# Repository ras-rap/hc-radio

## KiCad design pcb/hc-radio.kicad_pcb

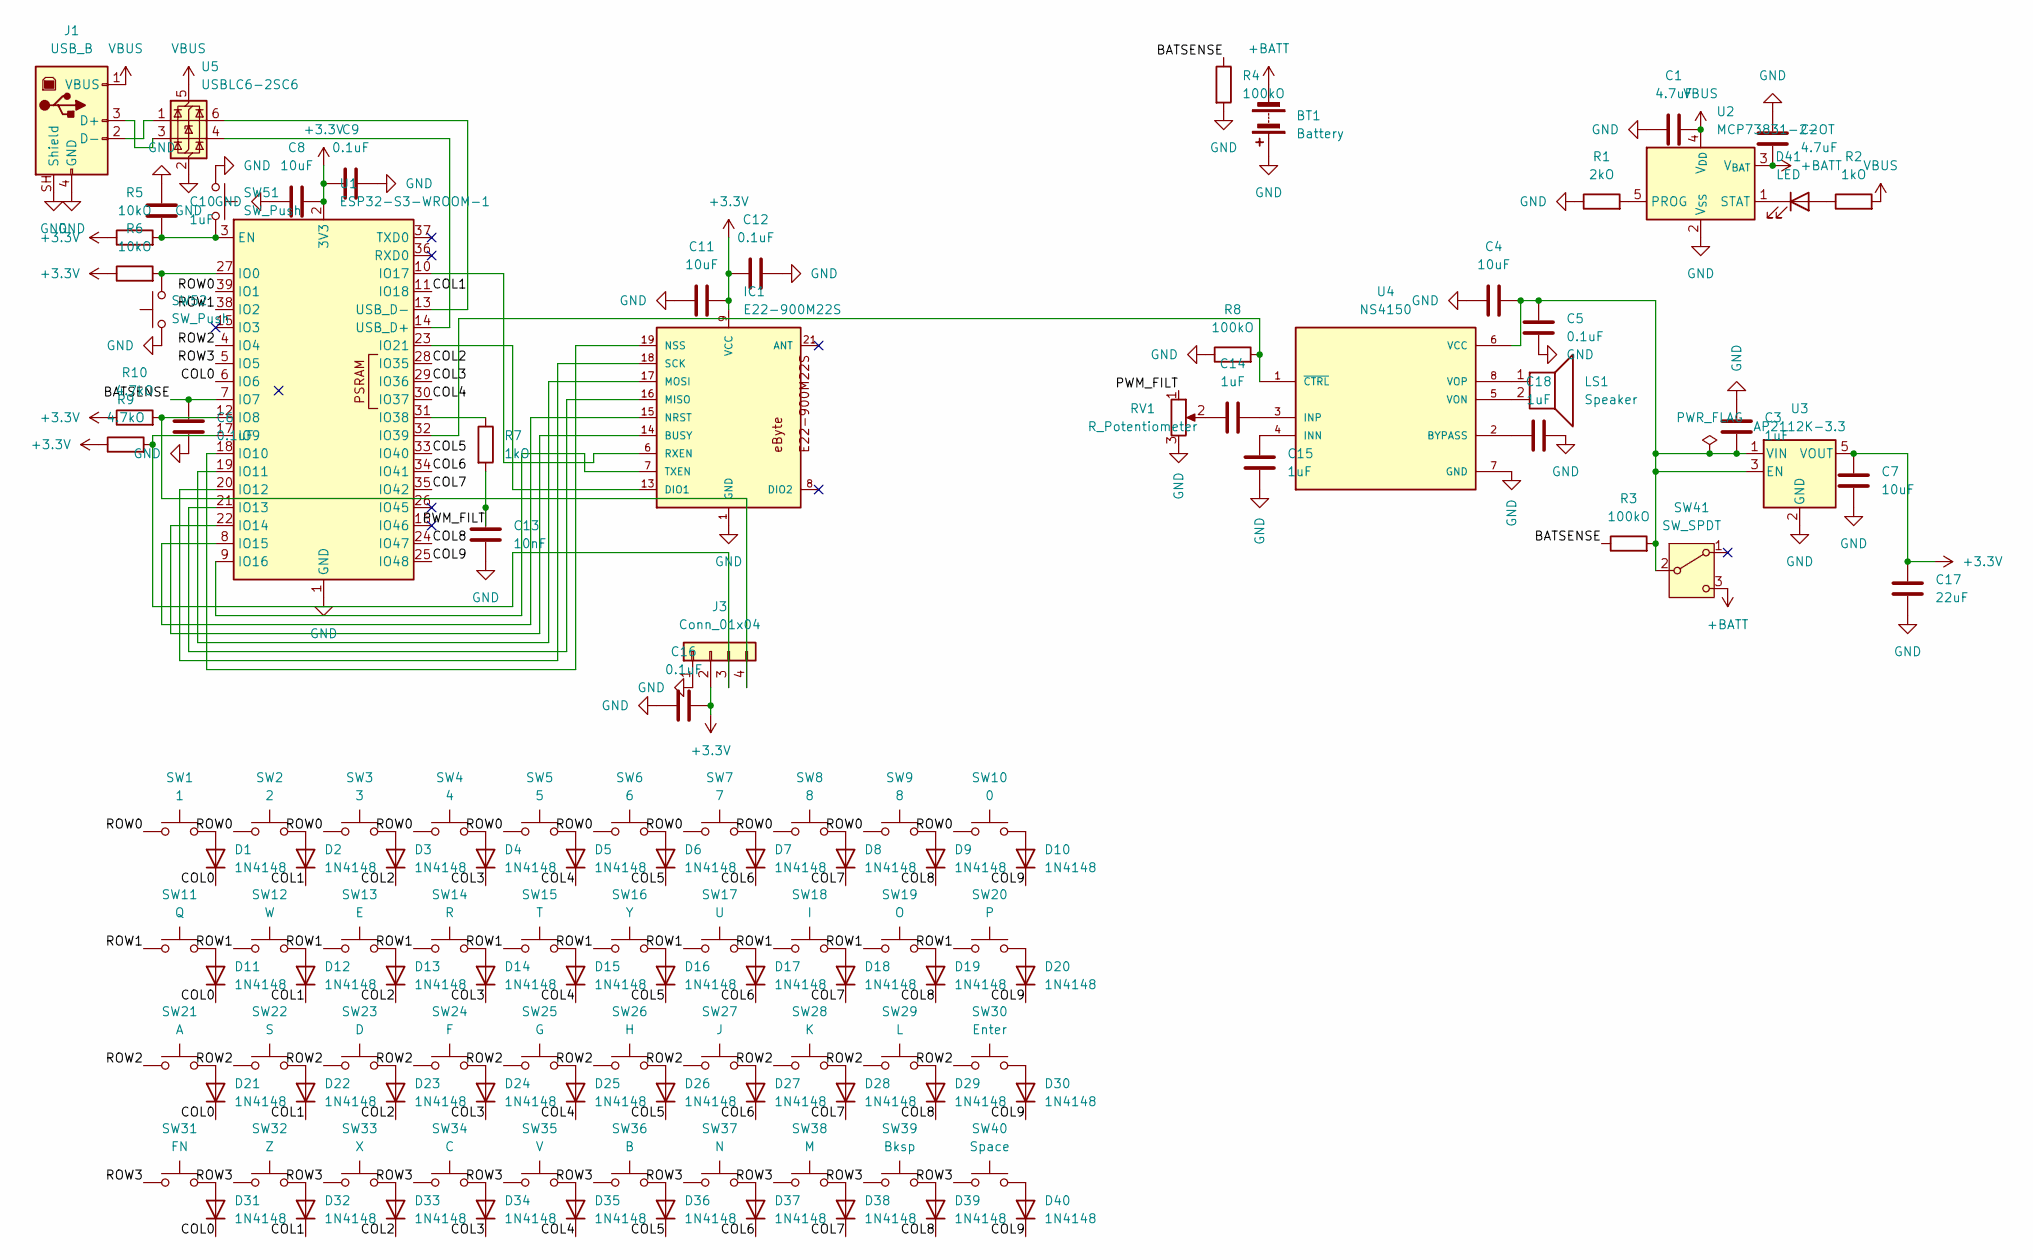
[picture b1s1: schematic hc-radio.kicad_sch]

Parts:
BT1: Battery; JST_PH_B2B-PH-K_1x02_P2.00mm_Vertical
C1, C2: 4.7uF; C_0805_2012Metric_Pad1.18x1.45mm_HandSolder
C3, C10, C14, C15, C18: 1uF; C_0805_2012Metric_Pad1.18x1.45mm_HandSolder
C4, C7, C8, C11: 10uF; C_0805_2012Metric_Pad1.18x1.45mm_HandSolder
C5, C6, C9, C12, C16: 0.1uF; C_0805_2012Metric_Pad1.18x1.45mm_HandSolder
C13: 10nF; C_0805_2012Metric_Pad1.18x1.45mm_HandSolder
C17: 22uF; C_0805_2012Metric_Pad1.18x1.45mm_HandSolder
D1, D2, D3, D4, D5, D6, D7, D8, D9, D10, D11, D12, D13, D14, D15, D16, D17, D18, D19, D20, D21, D22, D23, D24, D25, D26, D27, D28, D29, D30, D31, D32, D33, D34, D35, D36, D37, D38, D39, D40: 1N4148; D_DO-35_SOD27_P7.62mm_Horizontal
D41: LED; LED_D3.0mm
IC1: E22-900M22S
J1: USB_B; USB_B_Lumberg_2411_02_Horizontal
J3: Conn_01x04; PinHeader_1x04_P2.54mm_Vertical
LS1: Speaker; JST_EH_B2B-EH-A_1x02_P2.50mm_Vertical
R1: 2kO; R_0805_2012Metric_Pad1.20x1.40mm_HandSolder
R2, R7: 1kO; R_0805_2012Metric_Pad1.20x1.40mm_HandSolder
R3, R4, R8: 100kO; R_0805_2012Metric_Pad1.20x1.40mm_HandSolder
R5, R6: 10kO; R_0805_2012Metric_Pad1.20x1.40mm_HandSolder
R9, R10: 4.7kO; R_0805_2012Metric_Pad1.20x1.40mm_HandSolder
RV1: R_Potentiometer; Potentiometer_Alps_RK163_Single_Horizontal
SW1: 1; SW_PUSH_6mm
SW2: 2; SW_PUSH_6mm
SW3: 3; SW_PUSH_6mm
SW4: 4; SW_PUSH_6mm
SW5: 5; SW_PUSH_6mm
SW6: 6; SW_PUSH_6mm
SW7: 7; SW_PUSH_6mm
SW8, SW9: 8; SW_PUSH_6mm
SW10: 0; SW_PUSH_6mm
SW11: Q; SW_PUSH_6mm
SW12: W; SW_PUSH_6mm
SW13: E; SW_PUSH_6mm
SW14: R; SW_PUSH_6mm
SW15: T; SW_PUSH_6mm
SW16: Y; SW_PUSH_6mm
SW17: U; SW_PUSH_6mm
SW18: I; SW_PUSH_6mm
SW19: O; SW_PUSH_6mm
SW20: P; SW_PUSH_6mm
SW21: A; SW_PUSH_6mm
SW22: S; SW_PUSH_6mm
SW23: D; SW_PUSH_6mm
SW24: F; SW_PUSH_6mm
SW25: G; SW_PUSH_6mm
SW26: H; SW_PUSH_6mm
SW27: J; SW_PUSH_6mm
SW28: K; SW_PUSH_6mm
SW29: L; SW_PUSH_6mm
SW30: Enter; SW_PUSH_6mm
SW31: FN; SW_PUSH_6mm
SW32: Z; SW_PUSH_6mm
SW33: X; SW_PUSH_6mm
SW34: C; SW_PUSH_6mm
SW35: V; SW_PUSH_6mm
SW36: B; SW_PUSH_6mm
SW37: N; SW_PUSH_6mm
SW38: M; SW_PUSH_6mm
SW39: Bksp; SW_PUSH_6mm
SW40: Space; SW_PUSH_6mm
SW41: SW_SPDT; SW_Slide_SPDT_Straight_CK_OS102011MS2Q
SW51, SW52: SW_Push; SW_PUSH_6mm
U1: ESP32-S3-WROOM-1
U2: MCP73831-2-OT; SOT-23-5
U3: AP2112K-3.3; SOT-23-5
U4: NS4150; SOIC-8_3.9x4.9mm_P1.27mm; PARTREV 1.1
U5: USBLC6-2SC6; SOT-23-6

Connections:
+3.3V: C7.1, C8.2, C9.1, C11.2, C12.1, C16.2, C17.1, IC1.9 (VCC), J3.2, R5.1, R6.1, R9.1, R10.1, U1.2 (3V3), U3.5 (VOUT)
+BATT: BT1.2 (-), C2.2, SW41.3 (C), U2.3 (V_{BAT})
/BATSENSE: C6.1, R3.1, R4.1, U1.7 (IO7)
/COL0: D1.1 (K), D11.1 (K), D21.1 (K), D31.1 (K), U1.6 (IO6)
/COL1: D2.1 (K), D12.1 (K), D22.1 (K), D32.1 (K), U1.11 (IO18)
/COL2: D3.1 (K), D13.1 (K), D23.1 (K), D33.1 (K), U1.28 (IO35)
/COL3: D4.1 (K), D14.1 (K), D24.1 (K), D34.1 (K), U1.29 (IO36)
/COL4: D5.1 (K), D15.1 (K), D25.1 (K), D35.1 (K), U1.30 (IO37)
/COL5: D6.1 (K), D16.1 (K), D26.1 (K), D36.1 (K), U1.33 (IO40)
/COL6: D7.1 (K), D17.1 (K), D27.1 (K), D37.1 (K), U1.34 (IO41)
/COL7: D8.1 (K), D18.1 (K), D28.1 (K), D38.1 (K), U1.35 (IO42)
/COL8: D9.1 (K), D19.1 (K), D29.1 (K), D39.1 (K), U1.24 (IO47)
/COL9: D10.1 (K), D20.1 (K), D30.1 (K), D40.1 (K), U1.25 (IO48)
/PWM_FILT: C13.1, R7.2, RV1.1
/ROW0: SW1.1, SW2.1, SW3.1, SW4.1, SW5.1, SW6.1, SW7.1, SW8.1, SW9.1, SW10.1, U1.39 (IO1)
/ROW1: SW11.1, SW12.1, SW13.1, SW14.1, SW15.1, SW16.1, SW17.1, SW18.1, SW19.1, SW20.1, U1.38 (IO2)
/ROW2: SW21.1, SW22.1, SW23.1, SW24.1, SW25.1, SW26.1, SW27.1, SW28.1, SW29.1, SW30.1, U1.4 (IO4)
/ROW3: SW31.1, SW32.1, SW33.1, SW34.1, SW35.1, SW36.1, SW37.1, SW38.1, SW39.1, SW40.1, U1.5 (IO5)
GND: BT1.1 (+), C1.1, C2.1, C3.1, C4.1, C5.2, C6.2, C7.2, C8.1, C9.2, C10.2, C11.1, C12.2, C13.2, C15.2, C16.1, C17.2, C18.1, IC1.1 (GND), IC1.2 (GND), IC1.3 (GND), IC1.4 (GND), IC1.5 (GND), IC1.10 (GND), IC1.11 (GND), IC1.12 (GND), IC1.20 (GND), IC1.22 (GND), J1.4 (GND), J1.SH (Shield), J3.1, R1.1, R4.2, R8.1, RV1.3, SW51.1, SW52.1, U1.1 (GND), U1.40 (GND), U1.41 (GND), U2.2 (V_{SS}), U3.2 (GND), U4.7 (GND), U5.2 (GND)
unnamed: C14.2, RV1.2
unnamed: D1.2 (A), SW1.2
unnamed: D2.2 (A), SW2.2
unnamed: D3.2 (A), SW3.2
unnamed: D4.2 (A), SW4.2
unnamed: D5.2 (A), SW5.2
unnamed: D6.2 (A), SW6.2
unnamed: D7.2 (A), SW7.2
unnamed: D8.2 (A), SW8.2
unnamed: D9.2 (A), SW9.2
unnamed: D10.2 (A), SW10.2
unnamed: D11.2 (A), SW11.2
unnamed: D12.2 (A), SW12.2
unnamed: D13.2 (A), SW13.2
unnamed: D14.2 (A), SW14.2
unnamed: D15.2 (A), SW15.2
unnamed: D16.2 (A), SW16.2
unnamed: D17.2 (A), SW17.2
unnamed: D18.2 (A), SW18.2
unnamed: D19.2 (A), SW19.2
unnamed: D20.2 (A), SW20.2
unnamed: D21.2 (A), SW21.2
unnamed: D22.2 (A), SW22.2
unnamed: D23.2 (A), SW23.2
unnamed: D24.2 (A), SW24.2
unnamed: D25.2 (A), SW25.2
unnamed: D26.2 (A), SW26.2
unnamed: D27.2 (A), SW27.2
unnamed: D28.2 (A), SW28.2
unnamed: D29.2 (A), SW29.2
unnamed: D30.2 (A), SW30.2
unnamed: D31.2 (A), SW31.2
unnamed: D32.2 (A), SW32.2
unnamed: D33.2 (A), SW33.2
unnamed: D34.2 (A), SW34.2
unnamed: D35.2 (A), SW35.2
unnamed: D36.2 (A), SW36.2
unnamed: D37.2 (A), SW37.2
unnamed: D38.2 (A), SW38.2
unnamed: D39.2 (A), SW39.2
unnamed: D40.2 (A), SW40.2
unnamed: D41.2 (A), R2.1
unnamed: D41.1 (K), U2.1 (STAT)
unnamed: IC1.14 (BUSY), U1.22 (IO14)
unnamed: IC1.13 (DIO1), U1.23 (IO21)
unnamed: IC1.16 (MISO), U1.21 (IO13)
unnamed: IC1.17 (MOSI), U1.19 (IO11)
unnamed: IC1.15 (NRST), U1.8 (IO15)
unnamed: IC1.19 (NSS), U1.18 (IO10)
unnamed: IC1.6 (RXEN), U1.10 (IO17)
unnamed: IC1.18 (SCK), U1.20 (IO12)
unnamed: IC1.7 (TXEN), U1.9 (IO16)
unnamed: J1.3 (D+), U5.3 (I/O2)
unnamed: J1.2 (D-), U5.1 (I/O1)
unnamed: J3.3, R9.2, U1.17 (IO9)
unnamed: J3.4, R10.2, U1.12 (IO8)
unnamed: C3.2, C4.2, C5.1, R3.2, SW41.2 (B), U3.1 (VIN), U3.3 (EN), U4.6 (VCC)
unnamed: C10.1, R5.2, SW51.2, U1.3 (EN)
unnamed: R6.2, SW52.2, U1.27 (IO0)
unnamed: R7.1, U1.31 (IO38)
unnamed: R8.2, U1.32 (IO39), U4.1 (~CTRL)
unnamed: U1.14 (USB_D+), U5.4 (I/O2)
unnamed: U1.13 (USB_D-), U5.6 (I/O1)
unnamed: R1.2, U2.5 (PROG)
unnamed: C18.2, U4.2 (BYPASS)
unnamed: C15.1, U4.4 (INN)
unnamed: C14.1, U4.3 (INP)
unnamed: LS1.2, U4.5 (VON)
unnamed: LS1.1, U4.8 (VOP)
VBUS: C1.2, J1.1 (VBUS), R2.2, U2.4 (V_{DD}), U5.5 (VBUS)

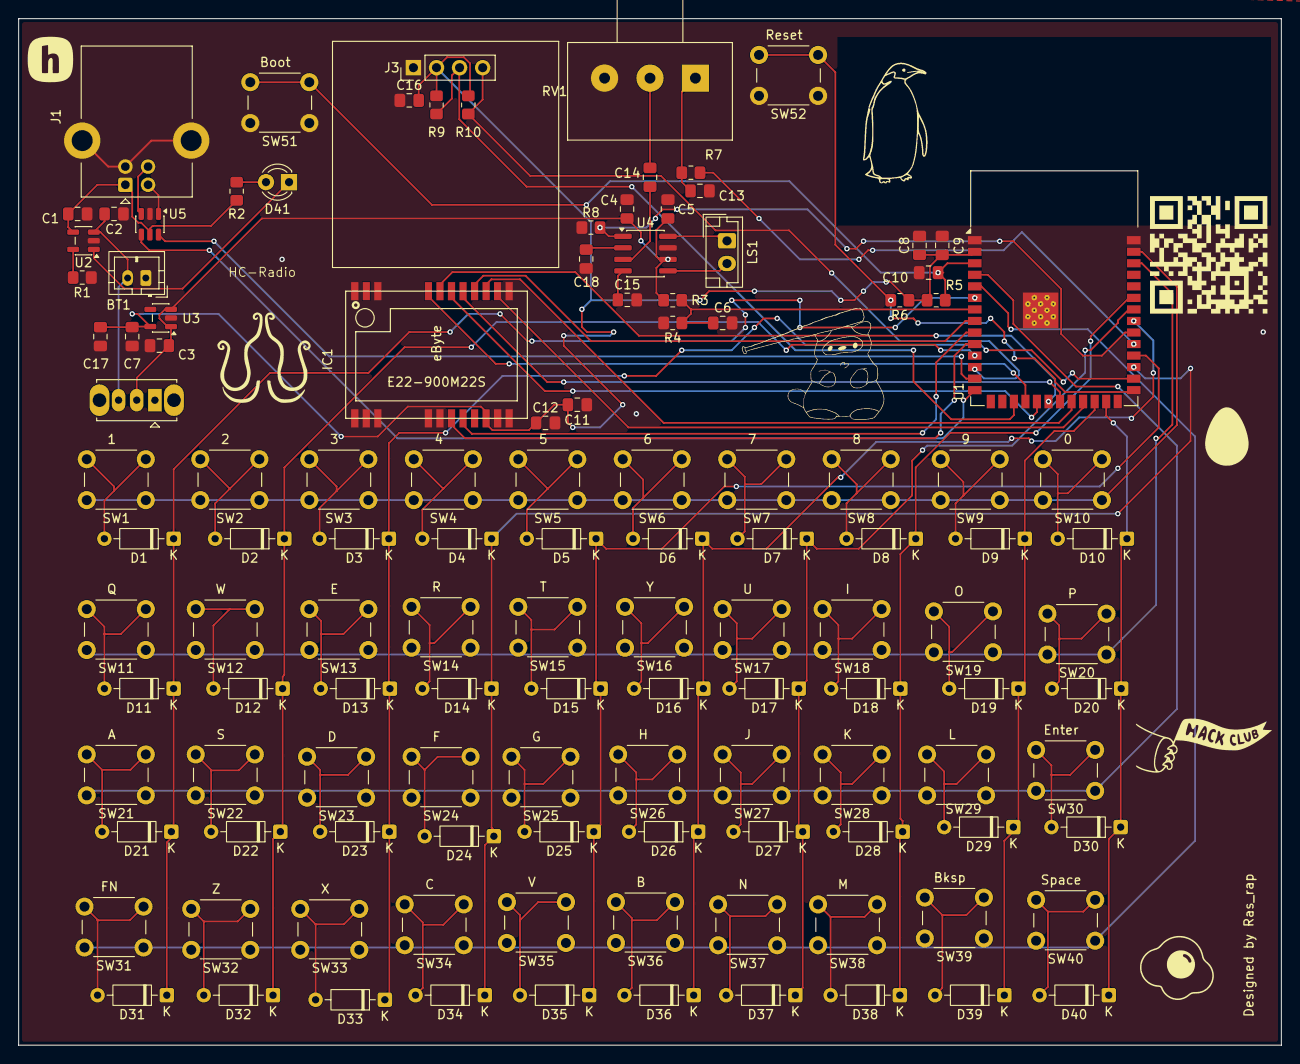
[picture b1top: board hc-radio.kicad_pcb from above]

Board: 2 copper layers, 139.0 x 113.0 mm, 123 parts (0 on the bottom side), 89 nets.

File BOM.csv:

Reference,Qty,Value,DNP,Exclude from BOM,Exclude from Board,Exclude from Simulation,Exclude from Position Files,Footprint,Datasheet
BT1,1,Battery,,,,,${EXCLUDE_FROM_POS_FILES},Connector_JST:JST_PH_B2B-PH-K_1x02_P2.00mm_Vertical,
"C1,C2",2,4.7uF,,,,,${EXCLUDE_FROM_POS_FILES},Capacitor_SMD:C_0805_2012Metric_Pad1.18x1.45mm_HandSolder,
"C3,C10,C14,C15,C18",5,1uF,,,,,${EXCLUDE_FROM_POS_FILES},Capacitor_SMD:C_0805_2012Metric_Pad1.18x1.45mm_HandSolder,
"C4,C7,C8,C11",4,10uF,,,,,${EXCLUDE_FROM_POS_FILES},Capacitor_SMD:C_0805_2012Metric_Pad1.18x1.45mm_HandSolder,
"C5,C6,C9,C12,C16",5,0.1uF,,,,,${EXCLUDE_FROM_POS_FILES},Capacitor_SMD:C_0805_2012Metric_Pad1.18x1.45mm_HandSolder,
C13,1,10nF,,,,,${EXCLUDE_FROM_POS_FILES},Capacitor_SMD:C_0805_2012Metric_Pad1.18x1.45mm_HandSolder,
C17,1,22uF,,,,,${EXCLUDE_FROM_POS_FILES},Capacitor_SMD:C_0805_2012Metric_Pad1.18x1.45mm_HandSolder,
"D1,D2,D3,D4,D5,D6,D7,D8,D9,D10,D11,D12,D13,D14,D15,D16,D17,D18,D19,D20,D21,D22,D23,D24,D25,D26,D27,D28,D29,D30,D31,D32,D33,D34,D35,D36,D37,D38,D39,D40",40,1N4148,,,,,${EXCLUDE_FROM_POS_FILES},Diode_THT:D_DO-35_SOD27_P7.62mm_Horizontal,https://assets.nexperia.com/documents/data-sheet/1N4148_1N4448.pdf
D41,1,LED,,,,,${EXCLUDE_FROM_POS_FILES},LED_THT:LED_D3.0mm,
IC1,1,E22-900M22S,,,,,${EXCLUDE_FROM_POS_FILES},E22-900M22S:E22-900M22S,
J1,1,USB_B,,,,,${EXCLUDE_FROM_POS_FILES},Connector_USB:USB_B_Lumberg_2411_02_Horizontal,
J3,1,Conn_01x04,,,,,${EXCLUDE_FROM_POS_FILES},Connector_PinHeader_2.54mm:PinHeader_1x04_P2.54mm_Vertical,
LS1,1,Speaker,,,,,${EXCLUDE_FROM_POS_FILES},Connector_JST:JST_EH_B2B-EH-A_1x02_P2.50mm_Vertical,
R1,1,2kO,,,,,${EXCLUDE_FROM_POS_FILES},Resistor_SMD:R_0805_2012Metric_Pad1.20x1.40mm_HandSolder,
"R2,R7",2,1kO,,,,,${EXCLUDE_FROM_POS_FILES},Resistor_SMD:R_0805_2012Metric_Pad1.20x1.40mm_HandSolder,
"R3,R4,R8",3,100kO,,,,,${EXCLUDE_FROM_POS_FILES},Resistor_SMD:R_0805_2012Metric_Pad1.20x1.40mm_HandSolder,
"R5,R6",2,10kO,,,,,${EXCLUDE_FROM_POS_FILES},Resistor_SMD:R_0805_2012Metric_Pad1.20x1.40mm_HandSolder,
"R9,R10",2,4.7kO,,,,,${EXCLUDE_FROM_POS_FILES},Resistor_SMD:R_0805_2012Metric_Pad1.20x1.40mm_HandSolder,
RV1,1,R_Potentiometer,,,,,${EXCLUDE_FROM_POS_FILES},Potentiometer_THT:Potentiometer_Alps_RK163_Single_Horizontal,
"SW1,SW2,SW3,SW4,SW5,SW6,SW7,SW8,SW9,SW10,SW11,SW12,SW13,SW14,SW15,SW16,SW17,SW18,SW19,SW20,SW21,SW22,SW23,SW24,SW25,SW26,SW27,SW28,SW29,SW30,SW31,SW32,SW33,SW34,SW35,SW36,SW37,SW38,SW39,SW40,SW51,SW52",42,*,,,,,${EXCLUDE_FROM_POS_FILES},Button_Switch_THT:SW_PUSH_6mm,
SW41,1,SW_SPDT,,,,,${EXCLUDE_FROM_POS_FILES},Button_Switch_THT:SW_Slide_SPDT_Straight_CK_OS102011MS2Q,
U1,1,ESP32-S3-WROOM-1,,,,,${EXCLUDE_FROM_POS_FILES},RF_Module:ESP32-S3-WROOM-1,https://www.espressif.com/sites/default/files/documentation/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
U2,1,MCP73831-2-OT,,,,,${EXCLUDE_FROM_POS_FILES},Package_TO_SOT_SMD:SOT-23-5,http://ww1.microchip.com/downloads/en/DeviceDoc/20001984g.pdf
U3,1,AP2112K-3.3,,,,,${EXCLUDE_FROM_POS_FILES},Package_TO_SOT_SMD:SOT-23-5,https://www.diodes.com/assets/Datasheets/AP2112.pdf
U4,1,NS4150,,,,,${EXCLUDE_FROM_POS_FILES},Package_SO:SOIC-8_3.9x4.9mm_P1.27mm,
U5,1,USBLC6-2SC6,,,,,${EXCLUDE_FROM_POS_FILES},Package_TO_SOT_SMD:SOT-23-6,https://www.st.com/resource/en/datasheet/usblc6-2.pdf
